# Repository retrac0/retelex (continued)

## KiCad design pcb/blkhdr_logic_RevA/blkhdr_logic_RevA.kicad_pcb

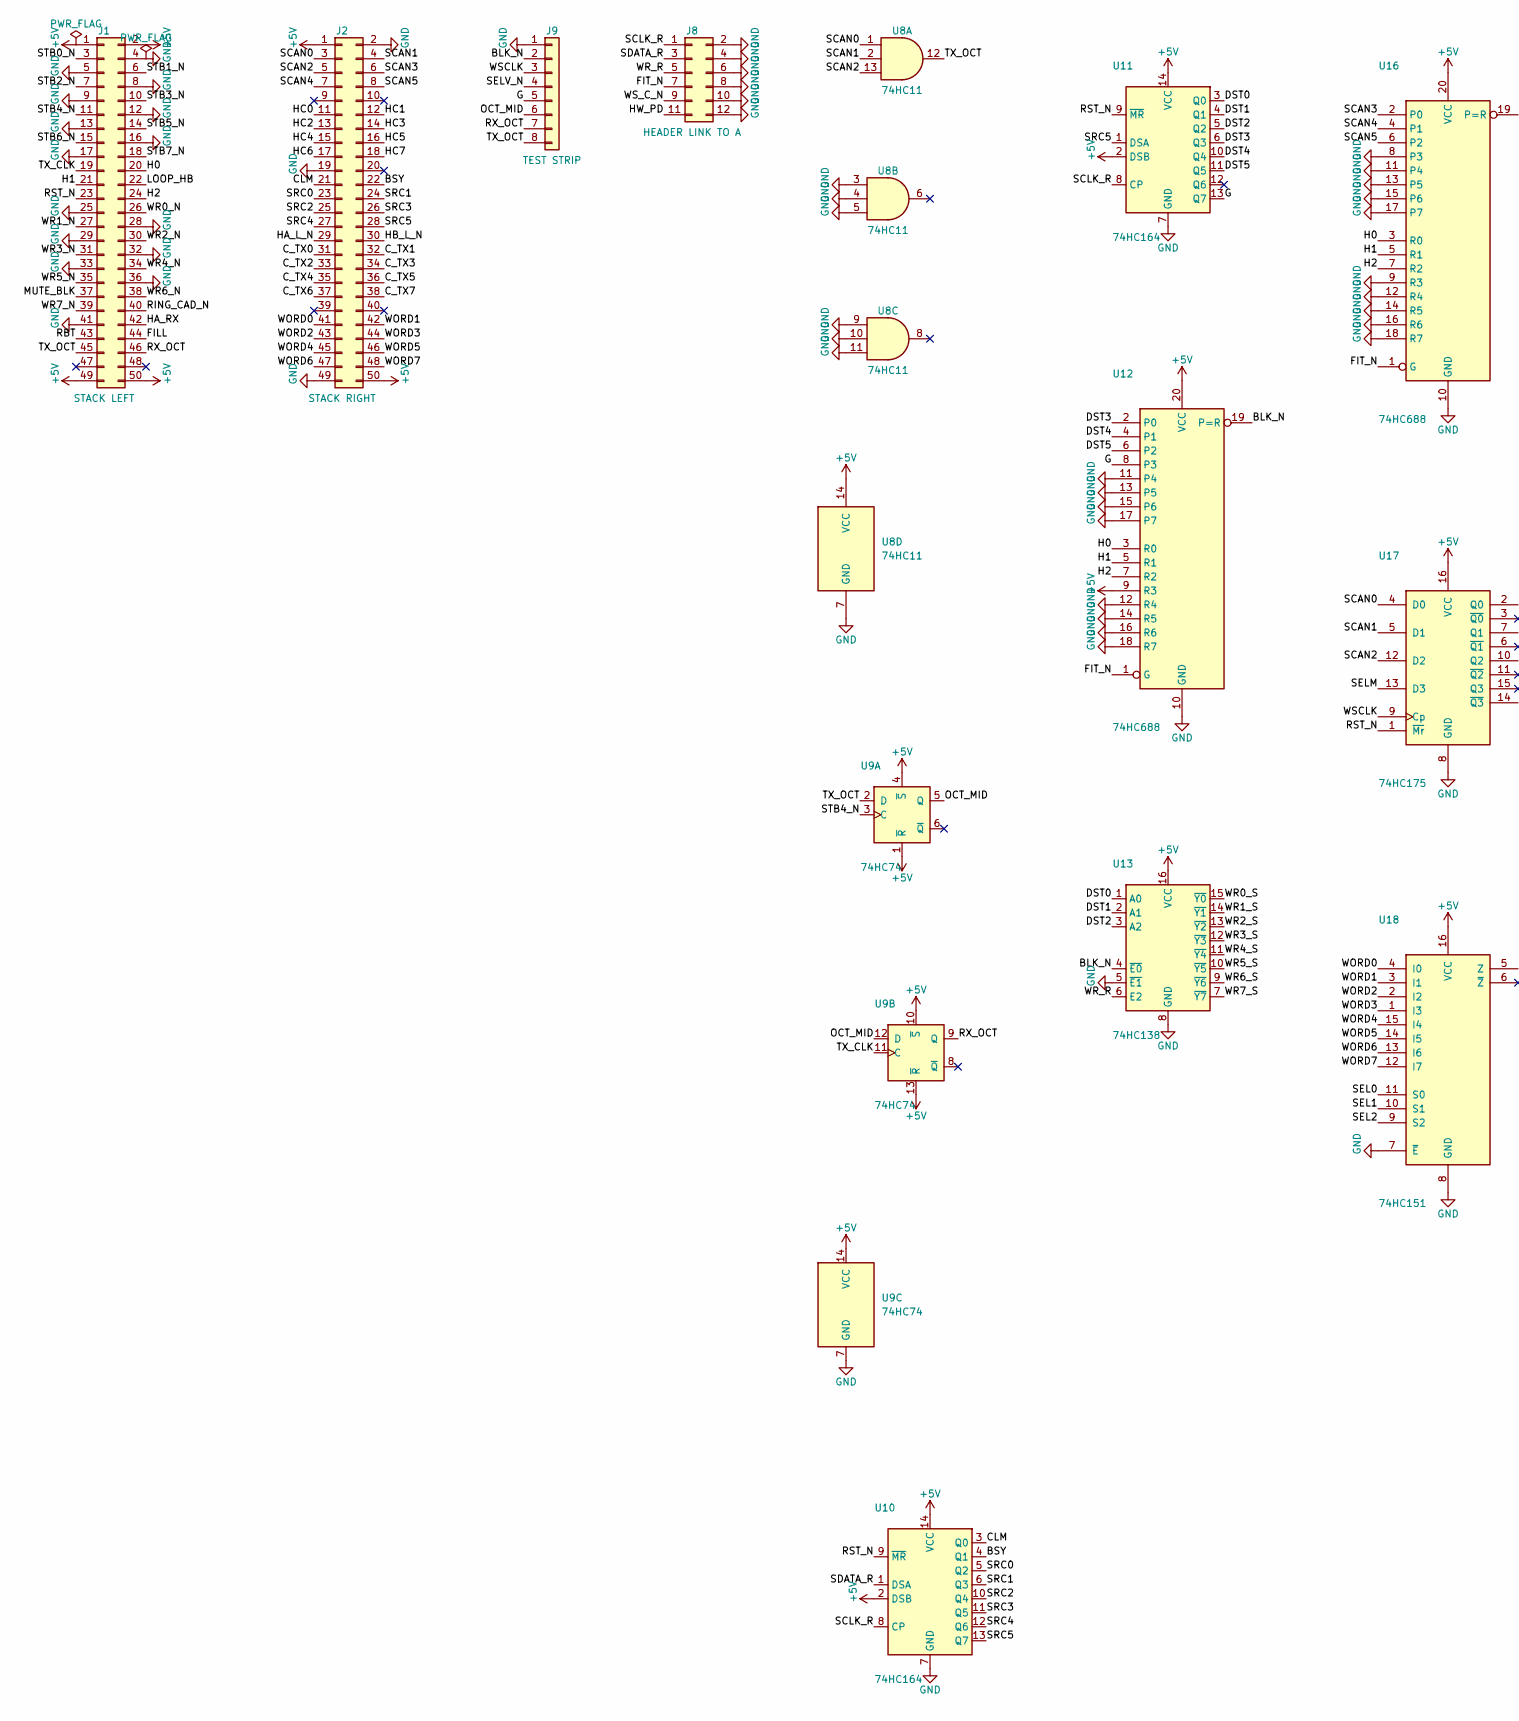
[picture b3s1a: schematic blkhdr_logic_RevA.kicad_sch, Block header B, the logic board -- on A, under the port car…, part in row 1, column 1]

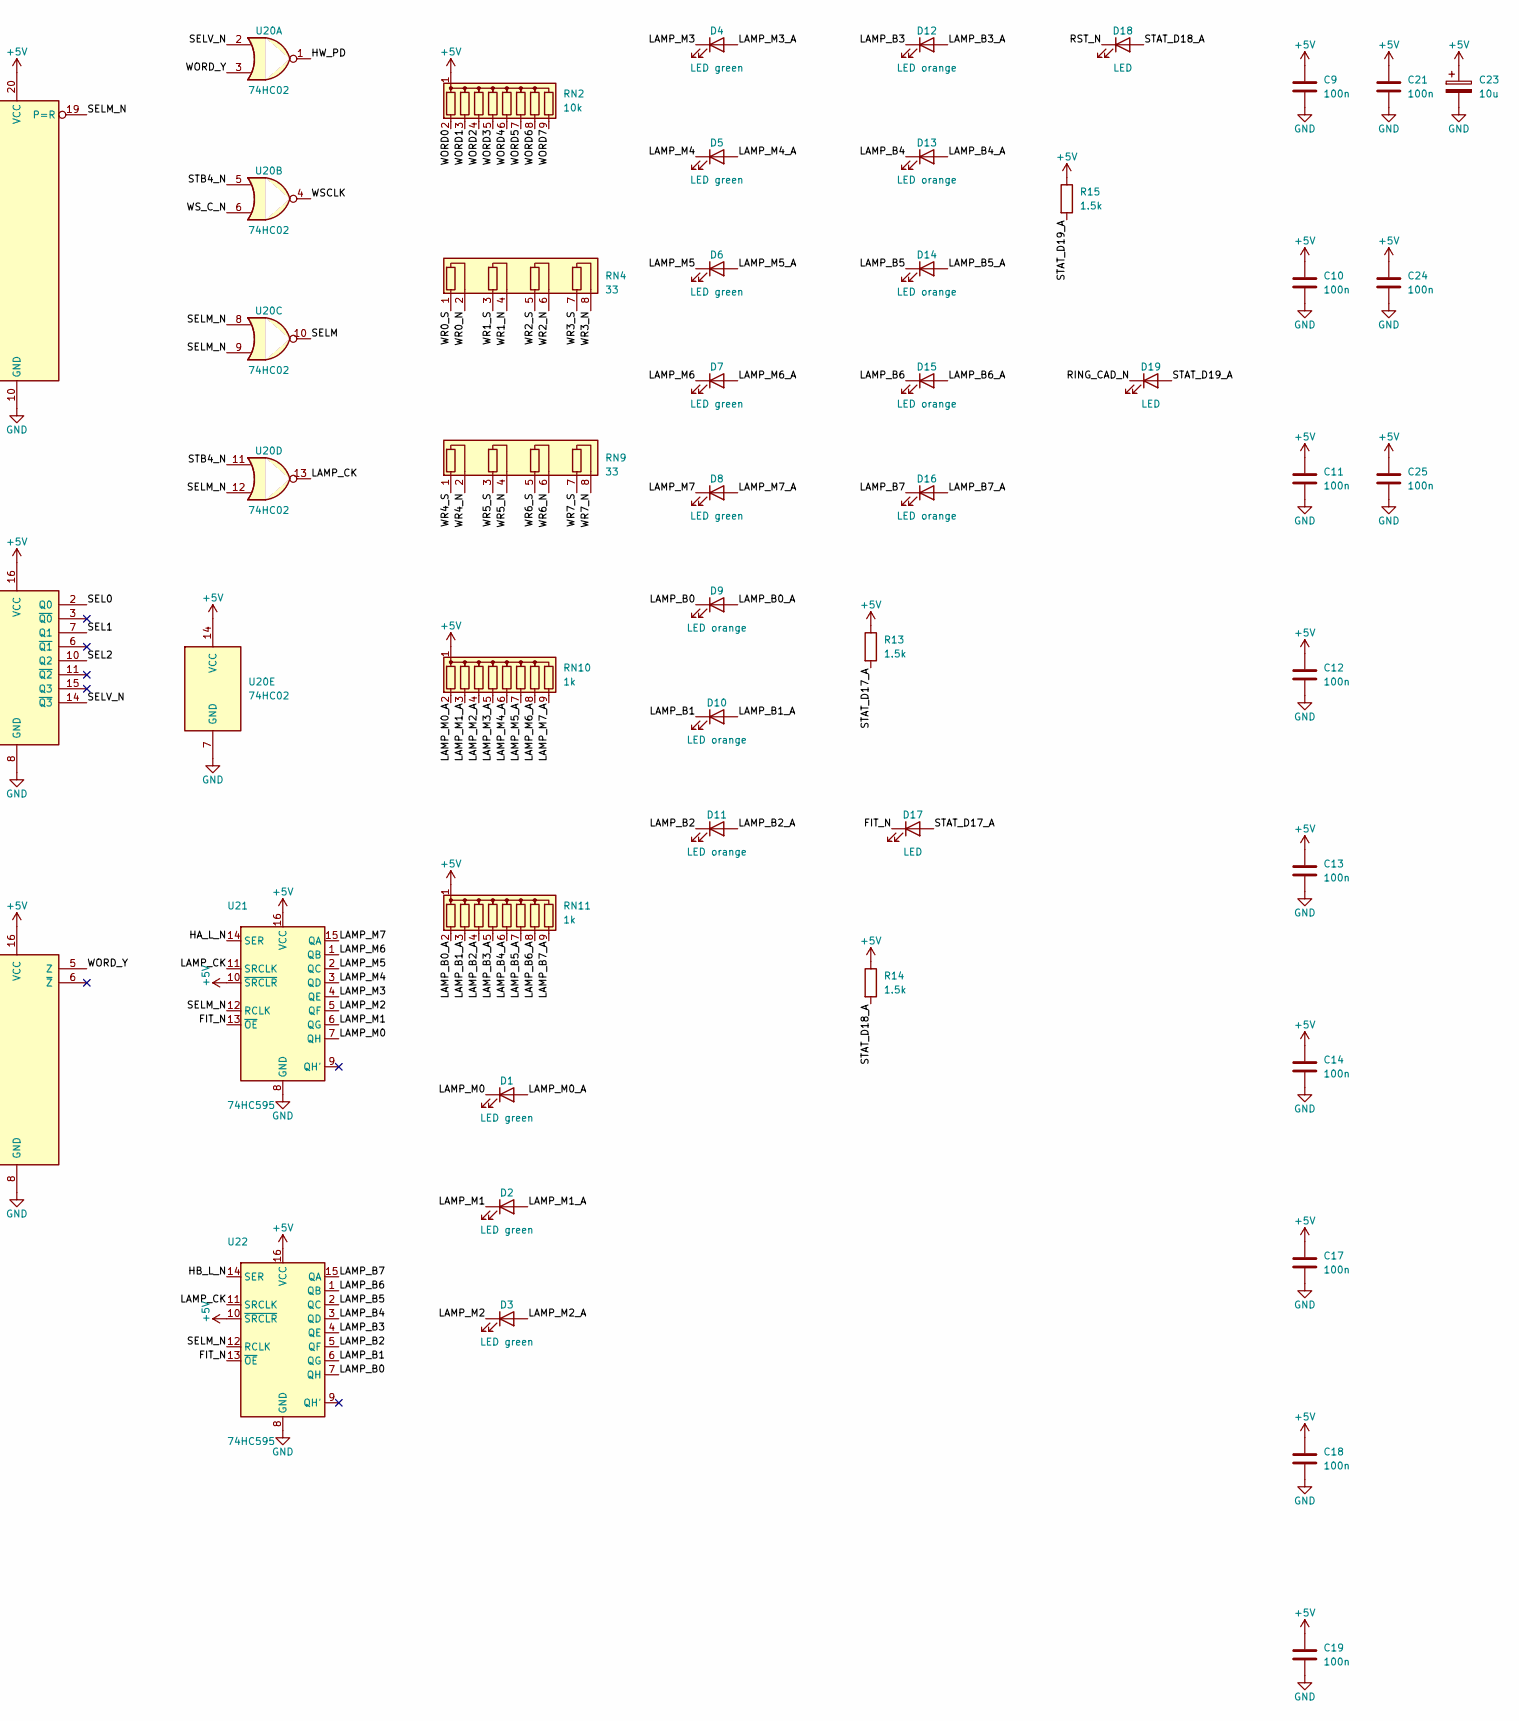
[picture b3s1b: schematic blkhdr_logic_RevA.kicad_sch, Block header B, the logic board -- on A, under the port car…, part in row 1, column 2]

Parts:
C9, C10, C11, C12, C13, C14, C17, C18, C19, C21, C24, C25: 100n; C_Disc_D3.0mm_W1.6mm_P2.50mm
C23: 10u; CP_Radial_D4.0mm_P1.50mm
D1, D2, D3, D4, D5, D6, D7, D8: LED green; LED_D3.0mm_Horizontal_Row
D9, D10, D11, D12, D13, D14, D15, D16: LED orange; LED_D3.0mm_Horizontal_Row
D17, D18, D19: LED; LED_D3.0mm
J1: STACK LEFT; Stack_2x25_P2.54mm_LongTail
J2: STACK RIGHT; Stack_2x25_P2.54mm_LongTail
J8: HEADER LINK TO A; PinHeader_2x06_P2.54mm_Vertical
J9: TEST STRIP; PinHeader_1x08_P2.54mm_Horizontal
R13, R14, R15: 1.5k; R_Axial_DIN0207_L6.3mm_D2.5mm_P2.54mm_Vertical
RN2: 10k; R_Array_SIP9
RN4, RN9: 33; R_Array_SIP8
RN10, RN11: 1k; R_Array_SIP9
U8: 74HC11; DIP-14_W7.62mm
U9: 74HC74; DIP-14_W7.62mm
U10, U11: 74HC164; DIP-14_W7.62mm
U12, U16: 74HC688; DIP-20_W7.62mm
U13: 74HC138; DIP-16_W7.62mm
U17: 74HC175; DIP-16_W7.62mm
U18: 74HC151; DIP-16_W7.62mm
U20: 74HC02; DIP-14_W7.62mm
U21, U22: 74HC595; DIP-16_W7.62mm

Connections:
+5V: C9.1, C10.1, C11.1, C12.1, C13.1, C14.1, C17.1, C18.1, C19.1, C21.1, C23.1, C24.1, C25.1, J1.1, J1.2, J1.49, J1.50, J2.1, J2.50, R13.1, R14.1, R15.1, RN2.1 (common), RN10.1 (common), RN11.1 (common), U8.14 (VCC), U9.1 (~R), U9.4 (~S), U9.10 (~S), U9.13 (~R), U9.14 (VCC), U10.2 (DSB), U10.14 (VCC), U11.2 (DSB), U11.14 (VCC), U12.9 (R3), U12.20 (VCC), U13.16 (VCC), U16.20 (VCC), U17.16 (VCC), U18.16 (VCC), U20.14 (VCC), U21.10 (~SRCLR), U21.16 (VCC), U22.10 (~SRCLR), U22.16 (VCC)
/BLK_N: J9.2, U12.19 (P=R), U13.4 (~E0)
/BSY: J2.22, U10.4 (Q1)
/CLM: J2.21, U10.3 (Q0)
/C_TX0: J2.31
/C_TX1: J2.32
/C_TX2: J2.33
/C_TX3: J2.34
/C_TX4: J2.35
/C_TX5: J2.36
/C_TX6: J2.37
/C_TX7: J2.38
/DST0: U11.3 (Q0), U13.1 (A0)
/DST1: U11.4 (Q1), U13.2 (A1)
/DST2: U11.5 (Q2), U13.3 (A2)
/DST3: U11.6 (Q3), U12.2 (P0)
/DST4: U11.10 (Q4), U12.4 (P1)
/DST5: U11.11 (Q5), U12.6 (P2)
/FILL: J1.44
/FIT_N: D17.1 (K), J8.7, U12.1 (G), U16.1 (G), U21.13 (~OE), U22.13 (~OE)
/G: J9.5, U11.13 (Q7), U12.8 (P3)
/H0: J1.20, U12.3 (R0), U16.3 (R0)
/H1: J1.21, U12.5 (R1), U16.5 (R1)
/H2: J1.24, U12.7 (R2), U16.7 (R2)
/HA_L_N: J2.29, U21.14 (SER)
/HA_RX: J1.42
/HB_L_N: J2.30, U22.14 (SER)
/HC0: J2.11
/HC1: J2.12
/HC2: J2.13
/HC3: J2.14
/HC4: J2.15
/HC5: J2.16
/HC6: J2.17
/HC7: J2.18
/HW_PD: J8.11, U20.1
/LAMP_B0: D9.1 (K), U22.7 (QH)
/LAMP_B0_A: D9.2 (A), RN11.2 (R1)
/LAMP_B1: D10.1 (K), U22.6 (QG)
/LAMP_B1_A: D10.2 (A), RN11.3 (R2)
/LAMP_B2: D11.1 (K), U22.5 (QF)
/LAMP_B2_A: D11.2 (A), RN11.4 (R3)
/LAMP_B3: D12.1 (K), U22.4 (QE)
/LAMP_B3_A: D12.2 (A), RN11.5 (R4)
/LAMP_B4: D13.1 (K), U22.3 (QD)
/LAMP_B4_A: D13.2 (A), RN11.6 (R5)
/LAMP_B5: D14.1 (K), U22.2 (QC)
/LAMP_B5_A: D14.2 (A), RN11.7 (R6)
/LAMP_B6: D15.1 (K), U22.1 (QB)
/LAMP_B6_A: D15.2 (A), RN11.8 (R7)
/LAMP_B7: D16.1 (K), U22.15 (QA)
/LAMP_B7_A: D16.2 (A), RN11.9 (R8)
/LAMP_CK: U20.13, U21.11 (SRCLK), U22.11 (SRCLK)
/LAMP_M0: D1.1 (K), U21.7 (QH)
/LAMP_M0_A: D1.2 (A), RN10.2 (R1)
/LAMP_M1: D2.1 (K), U21.6 (QG)
/LAMP_M1_A: D2.2 (A), RN10.3 (R2)
/LAMP_M2: D3.1 (K), U21.5 (QF)
/LAMP_M2_A: D3.2 (A), RN10.4 (R3)
/LAMP_M3: D4.1 (K), U21.4 (QE)
/LAMP_M3_A: D4.2 (A), RN10.5 (R4)
/LAMP_M4: D5.1 (K), U21.3 (QD)
/LAMP_M4_A: D5.2 (A), RN10.6 (R5)
/LAMP_M5: D6.1 (K), U21.2 (QC)
/LAMP_M5_A: D6.2 (A), RN10.7 (R6)
/LAMP_M6: D7.1 (K), U21.1 (QB)
/LAMP_M6_A: D7.2 (A), RN10.8 (R7)
/LAMP_M7: D8.1 (K), U21.15 (QA)
/LAMP_M7_A: D8.2 (A), RN10.9 (R8)
/LOOP_HB: J1.22
/MUTE_BLK: J1.37
/OCT_MID: J9.6, U9.5 (Q), U9.12 (D)
/RBT: J1.43
/RING_CAD_N: D19.1 (K), J1.40
/RST_N: D18.1 (K), J1.23, U10.9 (~MR), U11.9 (~MR), U17.1 (~Mr)
/RX_OCT: J1.46, J9.7, U9.9 (Q)
/SCAN0: J2.3, U8.1, U17.4 (D0)
/SCAN1: J2.4, U8.2, U17.5 (D1)
/SCAN2: J2.5, U8.13, U17.12 (D2)
/SCAN3: J2.6, U16.2 (P0)
/SCAN4: J2.7, U16.4 (P1)
/SCAN5: J2.8, U16.6 (P2)
/SCLK_R: J8.1, U10.8 (CP), U11.8 (CP)
/SDATA_R: J8.3, U10.1 (DSA)
/SEL0: U17.2 (Q0), U18.11 (S0)
/SEL1: U17.7 (Q1), U18.10 (S1)
/SEL2: U17.10 (Q2), U18.9 (S2)
/SELM: U17.13 (D3), U20.10
/SELM_N: U16.19 (P=R), U20.8, U20.9, U20.12, U21.12 (RCLK), U22.12 (RCLK)
/SELV_N: J9.4, U17.14 (~Q3), U20.2
/SRC0: J2.23, U10.5 (Q2)
/SRC1: J2.24, U10.6 (Q3)
/SRC2: J2.25, U10.10 (Q4)
/SRC3: J2.26, U10.11 (Q5)
/SRC4: J2.27, U10.12 (Q6)
/SRC5: J2.28, U10.13 (Q7), U11.1 (DSA)
/STAT_D17_A: D17.2 (A), R13.2
/STAT_D18_A: D18.2 (A), R14.2
/STAT_D19_A: D19.2 (A), R15.2
/STB0_N: J1.3
/STB1_N: J1.6
/STB2_N: J1.7
/STB3_N: J1.10
/STB4_N: J1.11, U9.3 (C), U20.5, U20.11
/STB5_N: J1.14
/STB6_N: J1.15
/STB7_N: J1.18
/TX_CLK: J1.19, U9.11 (C)
/TX_OCT: J1.45, J9.8, U8.12, U9.2 (D)
/WORD0: J2.41, RN2.2 (R1), U18.4 (I0)
/WORD1: J2.42, RN2.3 (R2), U18.3 (I1)
/WORD2: J2.43, RN2.4 (R3), U18.2 (I2)
/WORD3: J2.44, RN2.5 (R4), U18.1 (I3)
/WORD4: J2.45, RN2.6 (R5), U18.15 (I4)
/WORD5: J2.46, RN2.7 (R6), U18.14 (I5)
/WORD6: J2.47, RN2.8 (R7), U18.13 (I6)
/WORD7: J2.48, RN2.9 (R8), U18.12 (I7)
/WORD_Y: U18.5 (Z), U20.3
/WR0_N: J1.26, RN4.2 (R1.2)
/WR0_S: RN4.1 (R1.1), U13.15 (~Y0)
/WR1_N: J1.27, RN4.4 (R2.2)
/WR1_S: RN4.3 (R2.1), U13.14 (~Y1)
/WR2_N: J1.30, RN4.6 (R3.2)
/WR2_S: RN4.5 (R3.1), U13.13 (~Y2)
/WR3_N: J1.31, RN4.8 (R4.2)
/WR3_S: RN4.7 (R4.1), U13.12 (~Y3)
/WR4_N: J1.34, RN9.2 (R1.2)
/WR4_S: RN9.1 (R1.1), U13.11 (~Y4)
/WR5_N: J1.35, RN9.4 (R2.2)
/WR5_S: RN9.3 (R2.1), U13.10 (~Y5)
/WR6_N: J1.38, RN9.6 (R3.2)
/WR6_S: RN9.5 (R3.1), U13.9 (~Y6)
/WR7_N: J1.39, RN9.8 (R4.2)
/WR7_S: RN9.7 (R4.1), U13.7 (~Y7)
/WR_R: J8.5, U13.6 (E2)
/WSCLK: J9.3, U17.9 (Cp), U20.4
/WS_C_N: J8.9, U20.6
GND: C9.2, C10.2, C11.2, C12.2, C13.2, C14.2, C17.2, C18.2, C19.2, C21.2, C23.2, C24.2, C25.2, J1.4, J1.5, J1.8, J1.9, J1.12, J1.13, J1.16, J1.17, J1.25, J1.28, J1.29, J1.32, J1.33, J1.36, J1.41, J2.2, J2.19, J2.49, J8.2, J8.4, J8.6, J8.8, J8.10, J8.12, J9.1, U8.3, U8.4, U8.5, U8.7 (GND), U8.9, U8.10, U8.11, U9.7 (GND), U10.7 (GND), U11.7 (GND), U12.10 (GND), U12.11 (P4), U12.12 (R4), U12.13 (P5), U12.14 (R5), U12.15 (P6), U12.16 (R6), U12.17 (P7), U12.18 (R7), U13.5 (~E1), U13.8 (GND), U16.8 (P3), U16.9 (R3), U16.10 (GND), U16.11 (P4), U16.12 (R4), U16.13 (P5), U16.14 (R5), U16.15 (P6), U16.16 (R6), U16.17 (P7), U16.18 (R7), U17.8 (GND), U18.7 (~E), U18.8 (GND), U20.7 (GND), U21.8 (GND), U22.8 (GND)

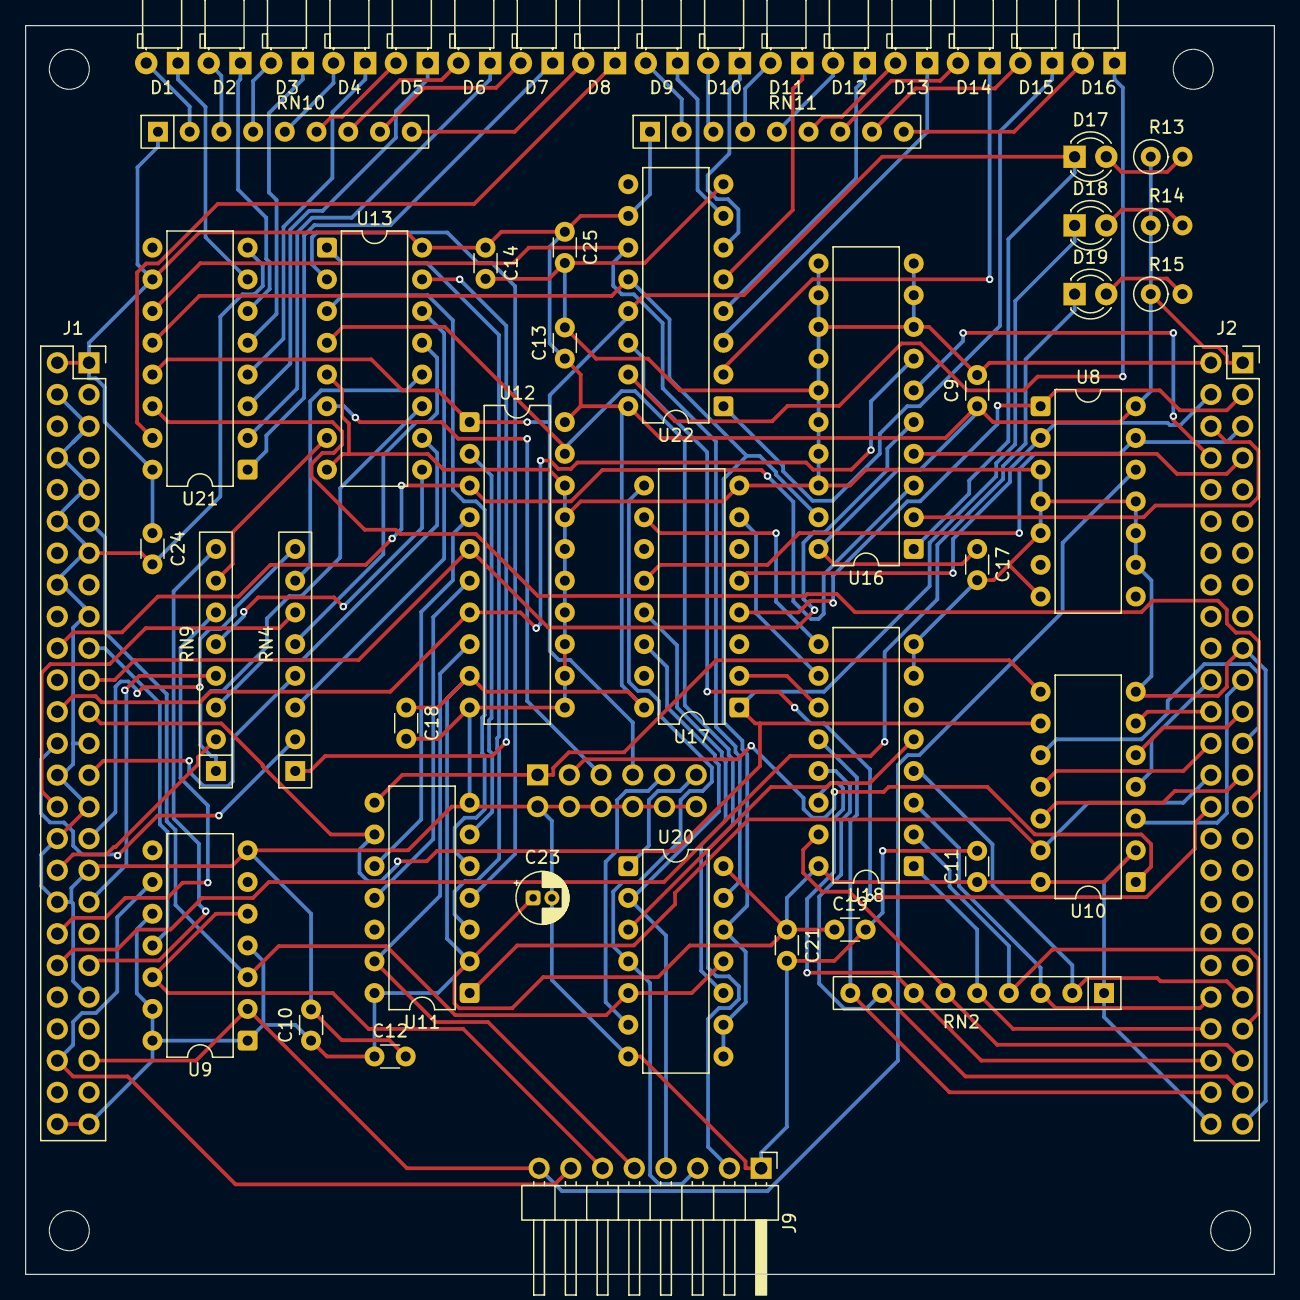
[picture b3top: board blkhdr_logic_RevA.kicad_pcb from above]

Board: 2 copper layers, 100.0 x 100.0 mm, 60 parts (1 on the bottom side), 110 nets.

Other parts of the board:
H1, H2, H3, H4: M3; MountingHole_3.2mm_M3

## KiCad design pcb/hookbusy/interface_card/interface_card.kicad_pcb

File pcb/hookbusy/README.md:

# Hook/busy PCB

KiCad 10 projects for the two boards in `exchange/proposed/lamps.md`, drawn for the
folded plane: both fields read the scanned `/HA` and `/HB` off cable A, and
nothing comes off cable B.

| Project | Role | Copies |
|---|---|---|
| [`lamp_card/`](lamp_card/) | One column of eight lamps + '259 + BLK/MODE | **16** |
| [`interface_card/`](interface_card/) | Cable A tap, '138 window decode onto `LE`, control '244, PWR inject | **1** |

The first placement came from a generator script (removed; see git history
before this commit). The boards are now edited by hand in KiCad. `make check`
in `pcb/` runs ERC and DRC on both.

Open `lamp_card/lamp_card.kicad_pro` or `interface_card/interface_card.kicad_pro` in KiCad 10.

## Locked for this layout pass

| | |
|---|---|
| Outline | **50 × 100 mm** (50 deep × 100 tall), 1.6 mm thick |
| Stack pitch | **0.4″ (10.16 mm)** — spacers are the datum; headers float |
| LED pitch | 0.4″ along the front edge (slot 0…7), centred on 100 mm |
| LED holes | **one** front-edge column, **D1…D8** only |
| Stuffing | HOOK green / BUSY orange in the same holes (by card MODE) |
| LED drive | anode to +5 V, cathode through **1k5** into the '259: lit while the latch is low (≈ 2 mA) |
| Stack headers | `J1` LE 1×8, `J3` PWR 1×4, `J4` control 1×6 — pin maps = `exchange/proposed/lamps.md` §3 |
| BLK | `JP1`, 2×8: one shunt routes `LE[h]` to the '259's `/LE` |
| MODE | `JP3`, 1×3 H\|C\|B: `/HA` or `/HB` into the '259's `D` |
| '259 | `A0..A2` = `SCAN[2:0]`, `/CLR` tied high |
| '138 (interface) | `A` = `SCAN[5:3]`, `/E1` = `HCLK`, `/E2` = `SLOTQ1`, `E3` = `SLOTQ2` → `LE0_N..LE7_N` |

## Status

- **PCB:** outline, footprints, nets on pads (ratsnest), no collisions. **Not routed.**
- **Schematic:** title-block stub only — draw next to match the refs on the board (`U1`, `D*`, `J*`, …).
- **Cable A tap `J5`:** a 2×8 placeholder, the eleven nets on pins 1–11 and GND on 12–16. The folded plane has no cable A pin table yet (`exchange/proposed/lamps.md` §3).
- **Stacking header P/N:** not chosen (need ~10.16 mm engagement).
- **Footprints** carry no library name (placed by the old script); "Update PCB from Schematic" will reassign them.

## Next

1. Draw schematics to match board refs (or reverse: schematic first, then Update PCB).
2. Pick stackable header + spacer; fix hole sizes.
3. Route; pour GND; DRC.
4. Bezel / panel drawing separate from these cards.

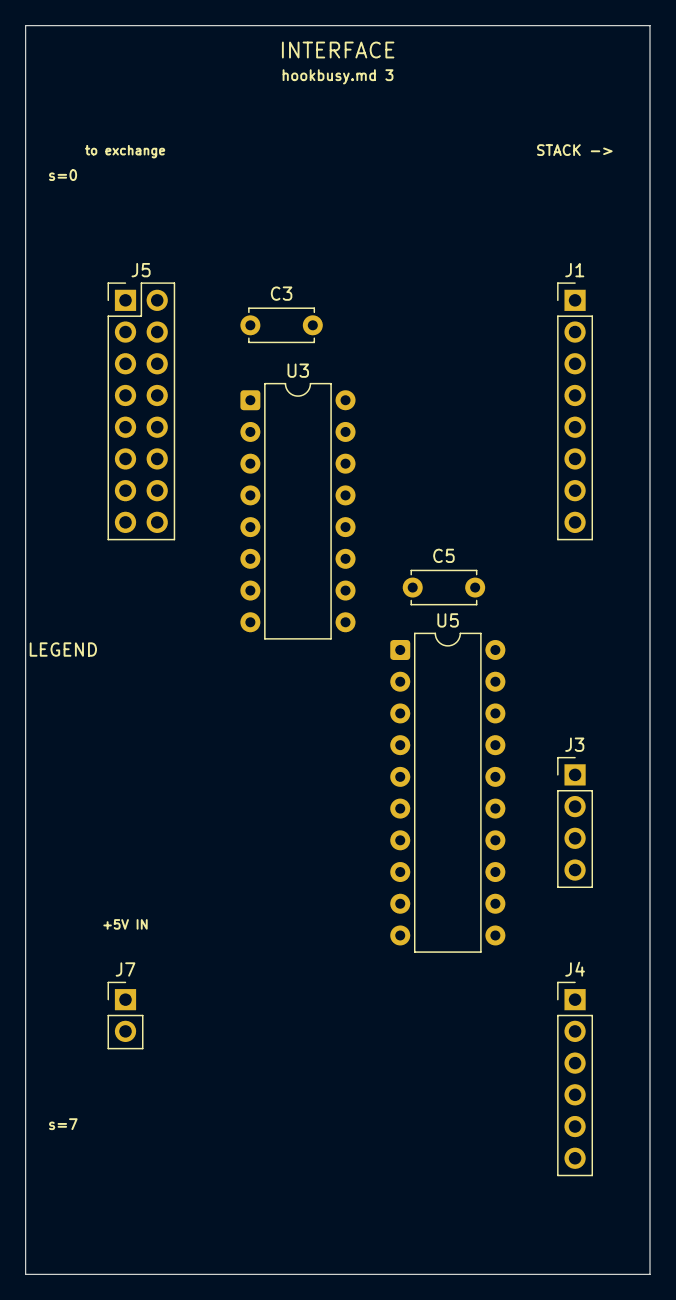
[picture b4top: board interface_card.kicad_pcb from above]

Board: 2 copper layers, 50.0 x 100.0 mm, 9 parts (0 on the bottom side), 26 nets, no tracks yet.

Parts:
C3, C5: 100n; C_Disc_D5.0mm_W2.5mm_P5.00mm
J1: LE; PinHeader_1x08_P2.54mm_Vertical
J3: PWR; PinHeader_1x04_P2.54mm_Vertical
J4: control; PinHeader_1x06_P2.54mm_Vertical
J5: CABLE_A_TAP; PinHeader_2x08_P2.54mm_Vertical
J7: PWR_IN; PinHeader_1x02_P2.54mm_Vertical
U3: 74HC138; DIP-16_W7.62mm
U5: 74HC244; DIP-20_W7.62mm

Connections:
+5V: C3.1, C5.1, J3.1, J3.3, J7.1, U3.16, U5.20
CBL_HA_N: J5.7, U5.8
CBL_HB_N: J5.8, U5.11
CBL_HCLK: J5.9, U3.4
CBL_SCAN0: J5.1, U5.2
CBL_SCAN1: J5.2, U5.4
CBL_SCAN2: J5.3, U5.6
CBL_SCAN3: J5.4, U3.1
CBL_SCAN4: J5.5, U3.2
CBL_SCAN5: J5.6, U3.3
CBL_SLOTQ1: J5.10, U3.5
CBL_SLOTQ2: J5.11, U3.6
GND: C3.2, C5.2, J3.2, J3.4, J5.12, J5.13, J5.14, J5.15, J5.16, J7.2, U3.8, U5.1, U5.10, U5.13, U5.15, U5.17, U5.19
HA_N: J4.4, U5.12
HB_N: J4.5, U5.9
LE0_N: J1.1, U3.15
LE1_N: J1.2, U3.14
LE2_N: J1.3, U3.13
LE3_N: J1.4, U3.12
LE4_N: J1.5, U3.11
LE5_N: J1.6, U3.10
LE6_N: J1.7, U3.9
LE7_N: J1.8, U3.7
SCAN0: J4.1, U5.18
SCAN1: J4.2, U5.16
SCAN2: J4.3, U5.14

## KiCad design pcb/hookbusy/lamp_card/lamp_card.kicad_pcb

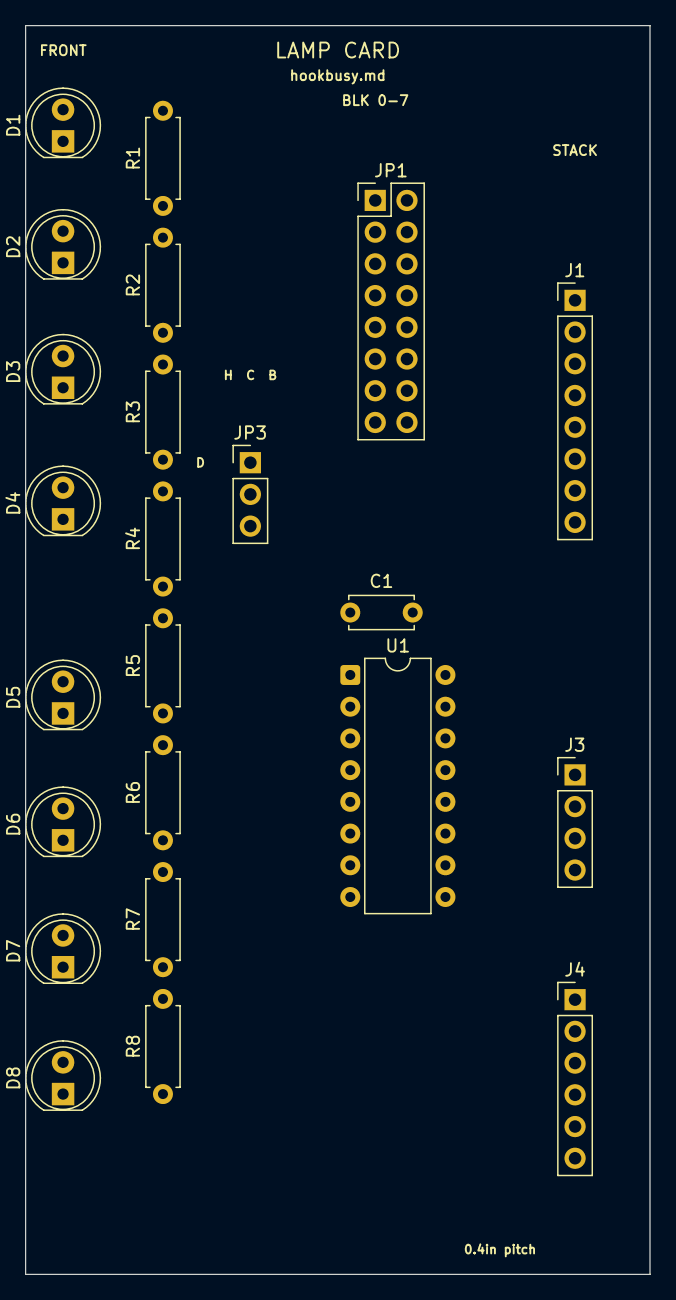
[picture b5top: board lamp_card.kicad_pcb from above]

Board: 2 copper layers, 50.0 x 100.0 mm, 23 parts (0 on the bottom side), 33 nets, no tracks yet.

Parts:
C1: 100n; C_Disc_D5.0mm_W2.5mm_P5.00mm
D1: LED_s0; LED_D5.0mm
D2: LED_s1; LED_D5.0mm
D3: LED_s2; LED_D5.0mm
D4: LED_s3; LED_D5.0mm
D5: LED_s4; LED_D5.0mm
D6: LED_s5; LED_D5.0mm
D7: LED_s6; LED_D5.0mm
D8: LED_s7; LED_D5.0mm
J1: LE; PinHeader_1x08_P2.54mm_Vertical
J3: PWR; PinHeader_1x04_P2.54mm_Vertical
J4: control; PinHeader_1x06_P2.54mm_Vertical
JP1: BLK; PinHeader_2x08_P2.54mm_Vertical
JP3: MODE; PinHeader_1x03_P2.54mm_Vertical
R1, R2, R3, R4, R5, R6, R7, R8: 1k5; R_Axial_DIN0207_L6.3mm_D2.5mm_P7.62mm_Horizontal
U1: 74HC259; DIP-16_W7.62mm

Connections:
+5V: C1.1, D1.2, D2.2, D3.2, D4.2, D5.2, D6.2, D7.2, D8.2, J3.1, J3.3, U1.15, U1.16
D: JP3.2, U1.13
GND: C1.2, J3.2, J3.4, U1.8
HA_N: J4.4, JP3.1
HB_N: J4.5, JP3.3
LE0_N: J1.1, JP1.1
LE1_N: J1.2, JP1.3
LE2_N: J1.3, JP1.5
LE3_N: J1.4, JP1.7
LE4_N: J1.5, JP1.9
LE5_N: J1.6, JP1.11
LE6_N: J1.7, JP1.13
LE7_N: J1.8, JP1.15
LED0: D1.1, R1.2
LED1: D2.1, R2.2
LED2: D3.1, R3.2
LED3: D4.1, R4.2
LED4: D5.1, R5.2
LED5: D6.1, R6.2
LED6: D7.1, R7.2
LED7: D8.1, R8.2
LE_N: JP1.2, JP1.4, JP1.6, JP1.8, JP1.10, JP1.12, JP1.14, JP1.16, U1.14
Q0: R1.1, U1.4
Q1: R2.1, U1.5
Q2: R3.1, U1.6
Q3: R4.1, U1.7
Q4: R5.1, U1.9
Q5: R6.1, U1.10
Q6: R7.1, U1.11
Q7: R8.1, U1.12
SCAN0: J4.1, U1.1
SCAN1: J4.2, U1.2
SCAN2: J4.3, U1.3

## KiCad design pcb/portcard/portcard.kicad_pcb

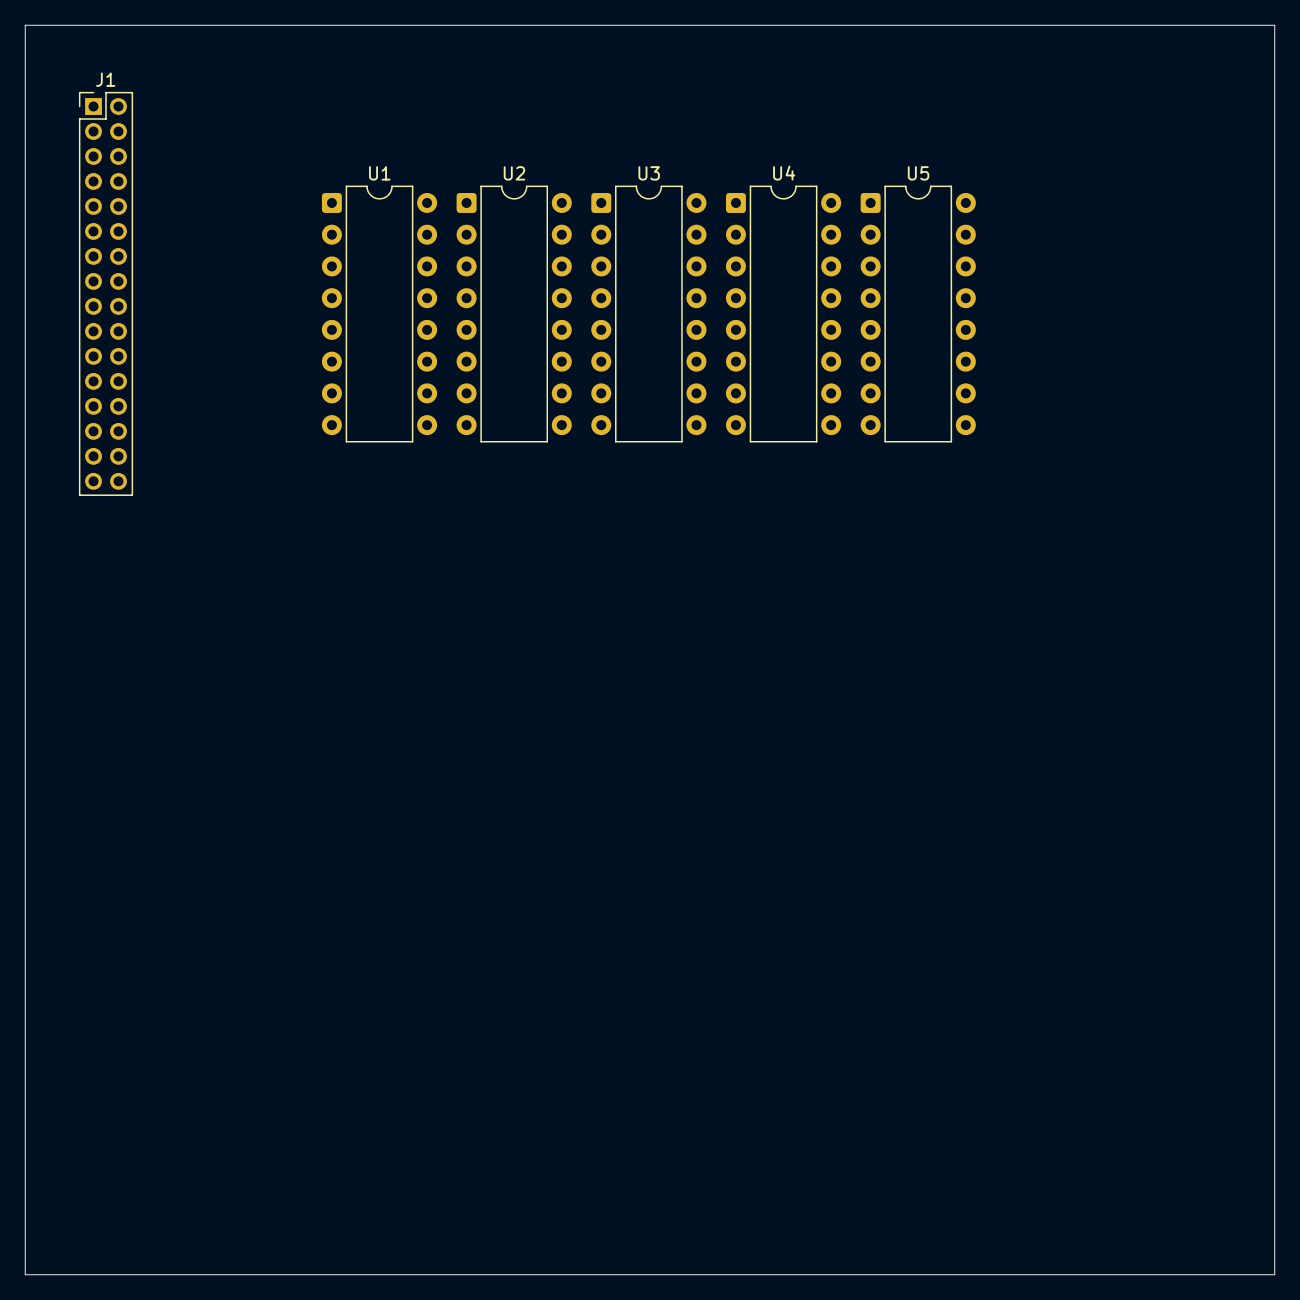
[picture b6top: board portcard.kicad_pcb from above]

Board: 2 copper layers, 100.0 x 100.0 mm, 6 parts (0 on the bottom side), 8 nets, no tracks yet.

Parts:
J1: PinHeader_2x16_P2.00mm_Vertical
U1: 74LS151; DIP-16_W7.62mm
U2, U3, U4, U5: 74LS153; DIP-16_W7.62mm

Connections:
unnamed: U1.4 (I0), U5.7 (Za)
unnamed: U1.3 (I1), U5.9 (Zb)
unnamed: U1.2 (I2), U4.7 (Za)
unnamed: U1.1 (I3), U4.9 (Zb)
unnamed: U1.15 (I4), U3.7 (Za)
unnamed: U1.14 (I5), U3.9 (Zb)
unnamed: U1.13 (I6), U2.7 (Za)
unnamed: U1.12 (I7), U2.9 (Zb)

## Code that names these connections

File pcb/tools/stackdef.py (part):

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    net(f"POS{i}", group="local", card=CP, drive="static, shunt to GND",
        pull=dict(to="+5V", ohm=10000, at="port card RN2"), rtl=f"POS[{i}] (port.v:28)")
net("BUSY_N", doc="/BUSY", group="local", card=CP, drive="totem-pole (U10)",
    rtl="busy (port.v:147); port_busy[k] = !BUSY_N", note="test point JP-TP pin 2")

# ----------------------------------------------------------------------------
# stack connectors: two 2x25, identical on every card (Joel, 2026-09-26).  Pin
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# stack nets.  A carries a 2x6 socket on top; B a plain 2x6 pin header on its
# UNDERSIDE, pins down into it -- 8.5 mm of socket and 2.54 mm of pin-header
# body mate at exactly the stack's 11 mm gap.  Nothing of it reaches a port card.
LINK_PINS = {1: "SCLK_R", 2: "GND", 3: "SDATA_R", 4: "GND", 5: "WR_R", 6: "GND",
             7: "FIT_N", 8: "GND", 9: "WS_C_N", 10: "GND", 11: "HW_PD", 12: "GND"}
LINK_POS = (41.0, 60.0)
LINK_A = dict(ref="J8", card=CA, role="header link to B (socket)",
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JP_POS = dict(ref="JP1", card=CP, label="POS", near="U5, the eq_own '688",
              footprint="Connector_PinHeader_2.54mm:PinHeader_2x03_P2.54mm_Vertical", side="top",
              rotation=90, pos=(50.0, 40.0), fixed=False,
              pins={1: "POS0", 2: "GND", 3: "POS1", 4: "GND", 5: "POS2", 6: "GND"},
              shunts=[dict(pads=[1, 2], means="S0: POS0 = 0"), dict(pads=[3, 4], means="S1: POS1 = 0"),
                      dict(pads=[5, 6], means="S2: POS2 = 0")],
              missing="an open position reads 1 (RN2 10k): no shunts at all is slot 7")
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JP_HC = dict(ref="JP1", card=CA, label="HC ROUTE", near="the bus's HC0-7 pins (J4 33-40) and R3",
             footprint="Connector_PinHeader_2.54mm:PinHeader_2x08_P2.54mm_Vertical", side="top",
             rotation=90, pos=(33.0, 83.0), fixed=False,
             pins={}, shunts=[], missing="HC_OUT reaches no highway: the block is silent on HC, and listens")
for j in range(8):
    h = 7 - j
    JP_HC["pins"][2 * j + 1] = f"B_HC{h}"
    JP_HC["pins"][2 * j + 2] = "HC_OUT"
    JP_HC["shunts"].append(dict(pads=[2 * j + 1, 2 * j + 2], means=f"HC_OUT drives highway HC{h}; must equal NUMBER h = {h}"))
JP_HC["pads"] = place(hdr2(8), JP_HC["pos"], 90)

JP_NUM = dict(ref="JP2", card=CA, label="NUMBER", near="RN7 and U4, the '244 that puts h up the stack",
              footprint="Connector_PinHeader_2.54mm:PinHeader_2x04_P2.54mm_Vertical", side="top",
              rotation=0, pos=(44.0, 30.0), fixed=False,
              pins={1: "FIT_N", 2: "GND", 3: "H0_J", 4: "GND", 5: "H1_J", 6: "GND", 7: "H2_J", 8: "GND"},
              shunts=[dict(pads=[1, 2], means="FIT: the block is fitted (JUMPERED)"),
                      dict(pads=[3, 4], means="h0 = 0"), dict(pads=[5, 6], means="h1 = 0"),
                      dict(pads=[7, 8], means="h2 = 0")],
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# reach bus pin 42.  On the ONE block of an exchange whose port card k is the
# ringback card, a shunt in column k puts lane C_TX k, through R12 (100R, as
# every bus driver: bus.md 2.4), onto B_RBT.  Open everywhere else.
JP_RBT = dict(ref="JP3", card=CA, label="RBT SOURCE", near="J2's C_TX pins, U15 and RN1; R12 at bus pin 42",
              footprint="Connector_PinHeader_2.54mm:PinHeader_2x08_P2.54mm_Vertical", side="top",
              rotation=0, pos=(87.5, 55.5), fixed=False, pins={}, shunts=[],
              missing="no shunt (every block but one): this block's lanes stay off the bus RBT")
for k in range(8):
    JP_RBT["pins"][2 * k + 1] = f"C_TX{k}"
    JP_RBT["pins"][2 * k + 2] = "RBT_SRC"
    JP_RBT["shunts"].append(dict(pads=[2 * k + 1, 2 * k + 2],
                                 means=f"lane {k}'s card is the exchange's ringback source: C_TX{k} drives RBT"))
JP_RBT["pads"] = place(hdr2(8), JP_RBT["pos"], 0)
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# A lamp is lit (Q low) while its card pulled the plane in its last turn: a pass
# (8 ms) behind, no scanning, DC.  /OE = /FIT: an unfitted block's lamps are dark.
def lamp_595(ref, plane, what):
    pins = {14: plane, 11: "LAMP_CK", 12: "SELM_N", 13: "FIT_N", 10: "+5V", 9: "NC"}
    for k in range(8):
        q = 7 - k
        pins[15 if q == 0 else q] = f"LAMP_{what}{k}"
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        "T_REL": "rc_det macro parameter on every detector cluster (sim only)"},
    ports=[
        ("clk", "in", "sim only: the HCLK shim and the rc_det / cr_rel macro cells; nothing on the boards"),
        ("rst_n", "in", "B_RESET_N (bus pin 23); the R11/C1 filter is a wire in simulation"),
        ("slot[2:0]", "in", "B_SLOT0..2 (bus 5, 7, 9)"),
        ("slotq[2:0]", "in", "B_SLOTQ0..2 (bus 11, 13, 15)"),
        ("cap_stb", "in", "sim only: rebuilds B_HCLK through the shim"),
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        ("ha_n", "in", "B_HA_N (bus 44), read by U6"),
        ("ha_pd", "out", "HA_PD: the gate of Q1"),
        ("hb_pd", "out", "HB_PD: the gate of Q2"),
        ("c_tx[7:0]", "in", "port card k's E_C_TX (edge a5, J4 pin 9); ignored where PORT_FITTED[k] = 0"),
        ("a_tx[7:0]", "in", "port card k's E_A_TX (a6, J4 pin 11)"),
        ("ans_n[7:0]", "in", "port card k's E_ANS_N (a13, J4 pin 25)"),
        ("word_n[7:0]", "in", "port card k's E_WORD (a12, J4 pin 23)"),
        ("c_rx[7:0]", "out", "port card k's E_C_RX (a9, J4 pin 17, after RN1); 0 where PORT_FITTED[k] = 0"),
        ("a_rx[7:0]", "out", "port card k's E_A_RX (a10, J4 pin 19, after RN1); 0 where PORT_FITTED[k] = 0"),
        ("mute_blk", "in", "A_MUTE_BLK (adapter J6 pin 7)"),
        ("sdata", "in", "B_SDATA (bus 21)"),
        ("sclk", "in", "B_SCLK (bus 17)"),
        ("wr", "in", "B_WR (bus 19)"),
        ("ws_n", "in", "B_WS_N (bus 47)"),
        ("hw_pd", "out", "HW_PD: the gate of Q3"),
        ("port_busy[7:0]", "out", "!BUSY_N of port card k (its J5 pin 2); 0 where PORT_FITTED[k] = 0")],
    hclk_shim="reg [1:0] n; always @(posedge clk or negedge rst_n) n <= !rst_n ? 0 : cap_stb ? 3 : (n != 0 ? n - 1 : 0); "
              "B_HCLK = !(cap_stb || n != 0)  -- low for ticks 4-7 exactly as clock_card.v:72",
    sim_only=["clk", "cap_stb -> B_HCLK shim", "tick_1k", "rc_det: D1/R6/R7/C1/U7.1 and D2/R8/R9/C2/U7.2 become a counter on tick_1k "
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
